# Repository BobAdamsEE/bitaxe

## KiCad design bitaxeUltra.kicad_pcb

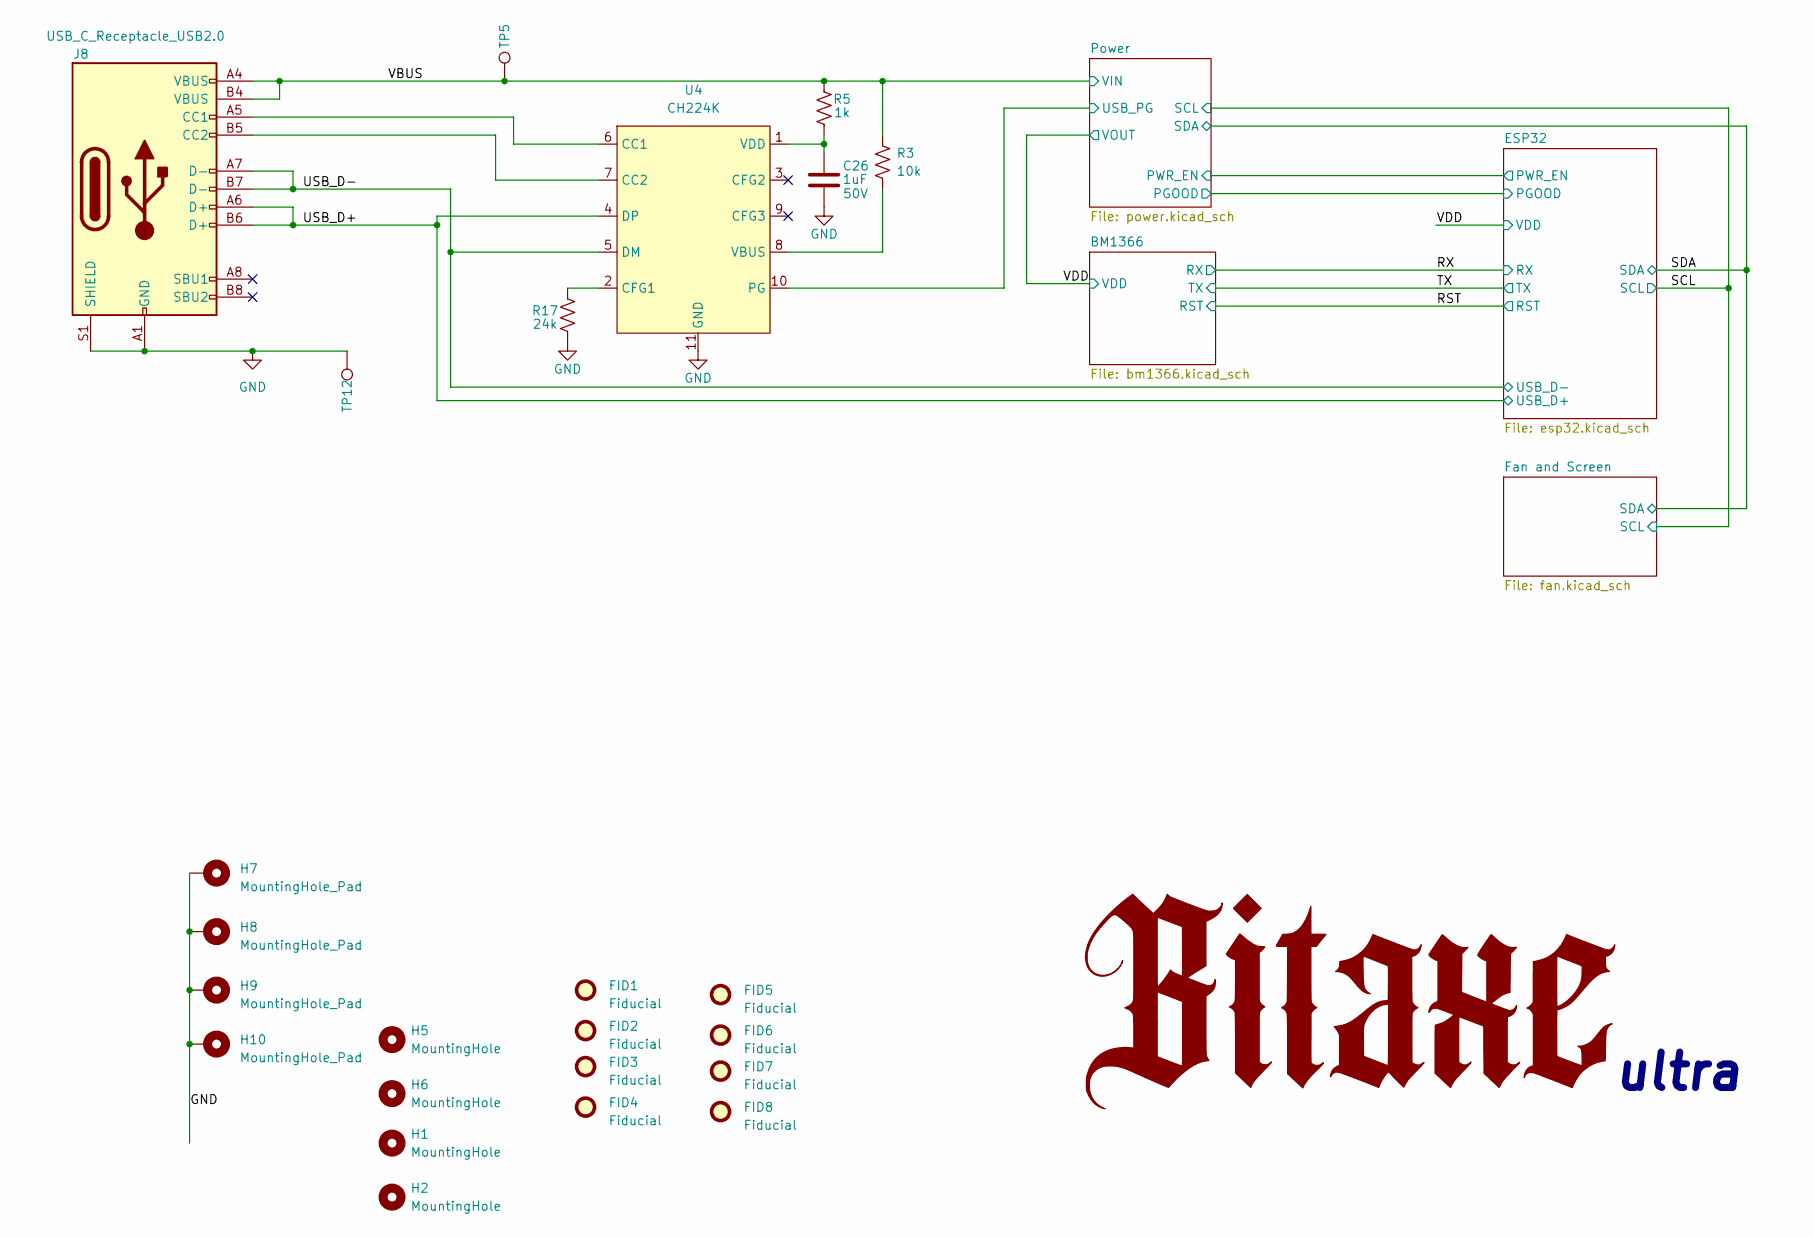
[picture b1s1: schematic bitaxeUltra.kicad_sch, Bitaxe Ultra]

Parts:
C26: 1uF; C_0603_1608Metric; Voltage 50V; PARTNO CC0603KRX7R9BB105
FID1, FID2, FID3, FID4, FID5, FID6, FID7, FID8: Fiducial; Fiducial_1mm_Mask2mm
H1, H2, H5, H6: MountingHole; MountingHole_3.5mm
H7, H8, H9, H10: MountingHole_Pad; MountingHole_3mm_Pad_Via
J8: USB_C_Receptacle_USB2.0; USB_C_Receptacle_GCT_USB4105-xx-A_16P_TopMnt_Horizontal; PARTNO USB4105-GF-A
R3: 10k; R_0402_1005Metric; PARTNO RC0402JR-0710KL
R5: 1k; R_0402_1005Metric; PARTNO RC0402JR-071KL
R17: 24k; R_0402_1005Metric; PARTNO RC0402JR-0724KL
TP5, TP12: TestPoint; TestPoint_Pad_D3.0mm
U4: CH224K; ESSOP-10; PARTNO CH224K

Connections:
/Power/USB_PG: U4.10 (PG); also elsewhere on the board
/USB_D+: J8.A6 (D+), J8.B6 (D+), U4.4 (DP); also elsewhere on the board
/USB_D-: J8.A7 (D-), J8.B7 (D-), U4.5 (DM); also elsewhere on the board
GND: C26.2, H7.1, H8.1, H9.1, H10.1, J8.A1 (GND), J8.B1 (GND), J8.S1 (SHIELD), R17.1, TP12.1, U4.11 (GND); also elsewhere on the board
IN+: J8.A4 (VBUS), J8.B4 (VBUS), R3.1, R5.2, TP5.1; also elsewhere on the board
unnamed: J8.A5 (CC1), U4.6 (CC1)
unnamed: J8.B5 (CC2), U4.7 (CC2)
unnamed: R17.2, U4.2 (CFG1)
unnamed: R3.2, U4.8 (VBUS)
unnamed: C26.1, R5.1, U4.1 (VDD)

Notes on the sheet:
ultra

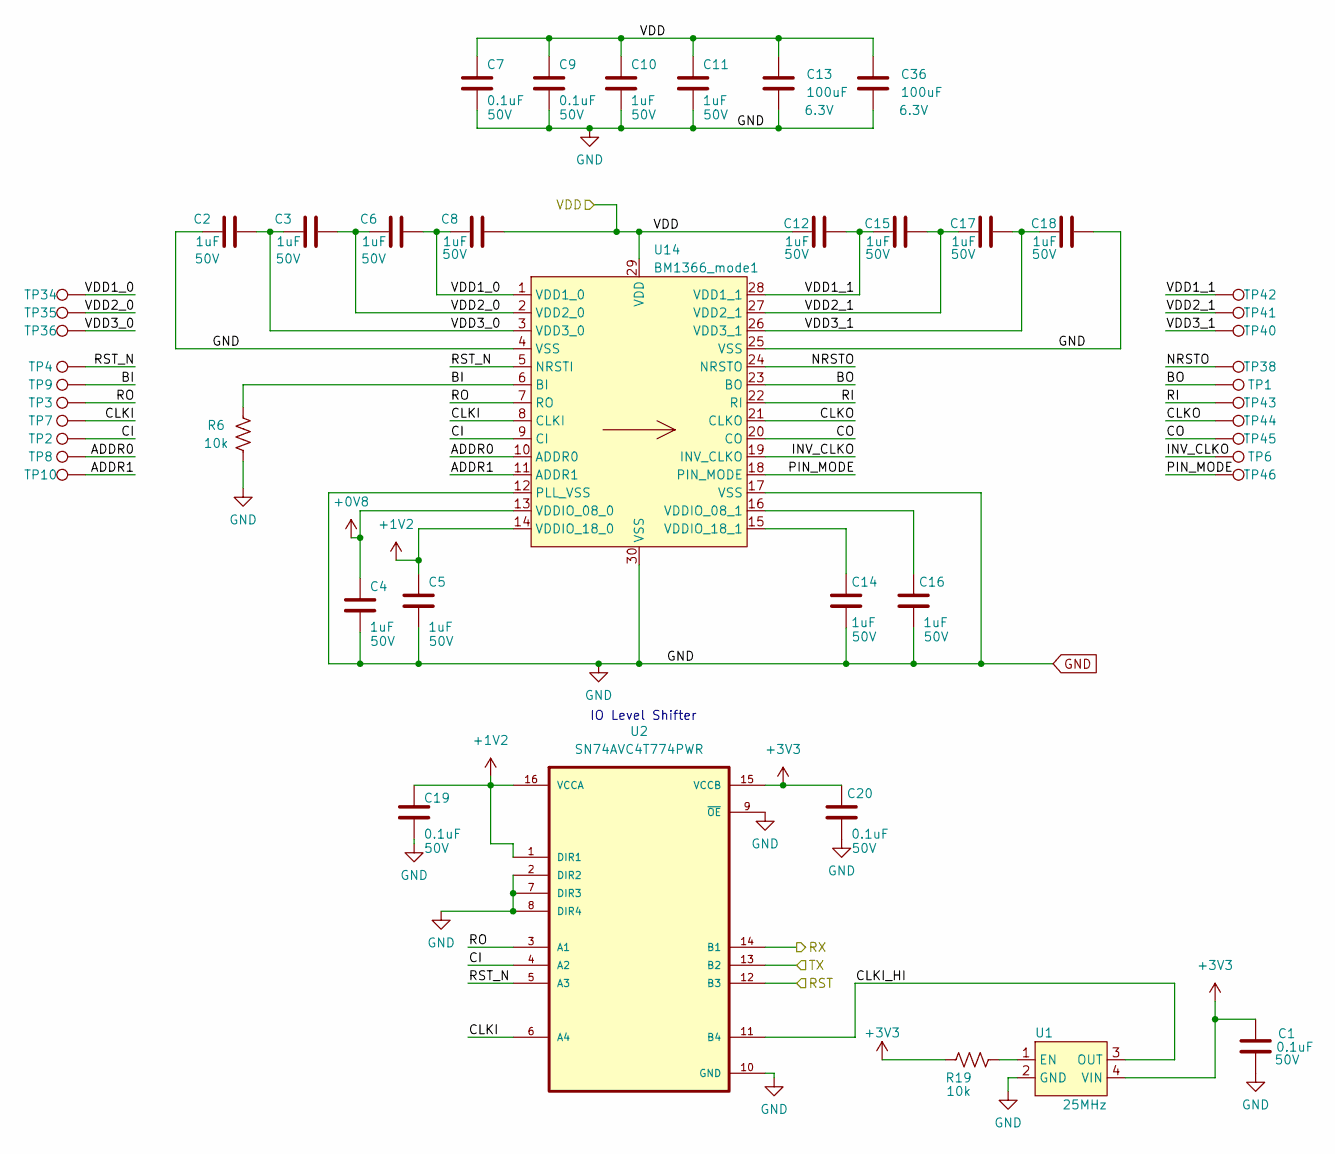
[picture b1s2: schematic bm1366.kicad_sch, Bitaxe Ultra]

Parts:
C1, C7, C9, C19, C20: 0.1uF; C_0402_1005Metric; Voltage 50V; PARTNO GRM155R71H104KE14J
C2, C3, C4, C5, C6, C8, C10, C11, C12, C14, C15, C16, C17, C18: 1uF; C_0603_1608Metric; Voltage 50V; PARTNO CC0603KRX7R9BB105
C13, C36: 100uF; C_1206_3216Metric; Voltage 6.3V; PARTNO GRM31CD80J107MEA8K
R6, R19: 10k; R_0402_1005Metric; PARTNO RC0402JR-0710KL
TP1, TP2, TP3, TP4, TP6, TP7, TP8, TP9, TP10, TP34, TP35, TP36, TP38, TP40, TP41, TP42, TP43, TP44, TP45, TP46: TestPoint; TestPoint_Pad_D1.5mm
U1: 25MHz; O 25,0-JO32-B-1V3-1-T1-LF; PARTNO O 25,0-JO32-B-1V3-1-T1-LF
U2: SN74AVC4T774PWR; SOP65P640X120-16N; PARTNO SN74AVC4T774PWR
U14: BM1366_mode1; BM1366

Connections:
+0V8: C4.1, U14.13 (VDDIO_08_0); also elsewhere on the board
+1V2: C5.1, C19.1, U2.1 (DIR1), U2.16 (VCCA), U14.14 (VDDIO_18_0); also elsewhere on the board
+3V3: C1.2, C20.1, R19.2, U1.4 (VIN), U2.15 (VCCB); also elsewhere on the board
/BM1366/ADDR0: TP8.1, U14.10 (ADDR0)
/BM1366/ADDR1: TP10.1, U14.11 (ADDR1)
/BM1366/BI: R6.2, TP9.1, U14.6 (BI)
/BM1366/BO: TP1.1, U14.23 (BO)
/BM1366/CI: TP2.1, U2.4 (A2), U14.9 (CI)
/BM1366/CLKI: TP7.1, U2.6 (A4), U14.8 (CLKI)
/BM1366/CLKI_HI: U1.3 (OUT), U2.11 (B4)
/BM1366/CLKO: TP44.1, U14.21 (CLKO)
/BM1366/CO: TP45.1, U14.20 (CO)
/BM1366/INV_CLKO: TP6.1, U14.19 (INV_CLKO)
/BM1366/NRSTO: TP38.1, U14.24 (NRSTO)
/BM1366/PIN_MODE: TP46.1, U14.18 (PIN_MODE)
/BM1366/RI: TP43.1, U14.22 (RI)
/BM1366/RO: TP3.1, U2.3 (A1), U14.7 (RO)
/BM1366/RST_N: TP4.1, U2.5 (A3), U14.5 (NRSTI)
/BM1366/VDD1_0: C6.2, C8.1, TP34.1, U14.1 (VDD1_0)
/BM1366/VDD1_1: C12.2, C15.1, TP42.1, U14.28 (VDD1_1)
/BM1366/VDD2_0: C3.2, C6.1, TP35.1, U14.2 (VDD2_0)
/BM1366/VDD2_1: C15.2, C17.1, TP41.1, U14.27 (VDD2_1)
/BM1366/VDD3_0: C2.2, C3.1, TP36.1, U14.3 (VDD3_0)
/BM1366/VDD3_1: C17.2, C18.1, TP40.1, U14.26 (VDD3_1)
/RST: U2.12 (B3); also elsewhere on the board
/RX: U2.14 (B1); also elsewhere on the board
/TX: U2.13 (B2); also elsewhere on the board
/VDD: C7.1, C8.2, C9.1, C10.1, C11.1, C12.1, C13.1, C36.1, U14.29 (VDD); also elsewhere on the board
GND: C1.1, C2.1, C4.2, C5.2, C7.2, C9.2, C10.2, C11.2, C13.2, C14.2, C16.2, C18.2, C19.2, C20.2, C36.2, R6.1, U1.2 (GND), U2.2 (DIR2), U2.7 (DIR3), U2.8 (DIR4), U2.9 (~OE), U2.10 (GND), U14.4 (VSS), U14.12 (PLL_VSS), U14.17 (VSS), U14.25 (VSS), U14.30 (VSS); also elsewhere on the board
unnamed: R19.1, U1.1 (EN)
unnamed: C16.1, U14.16 (VDDIO_08_1)
unnamed: C14.1, U14.15 (VDDIO_18_1)

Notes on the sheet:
IO Level Shifter

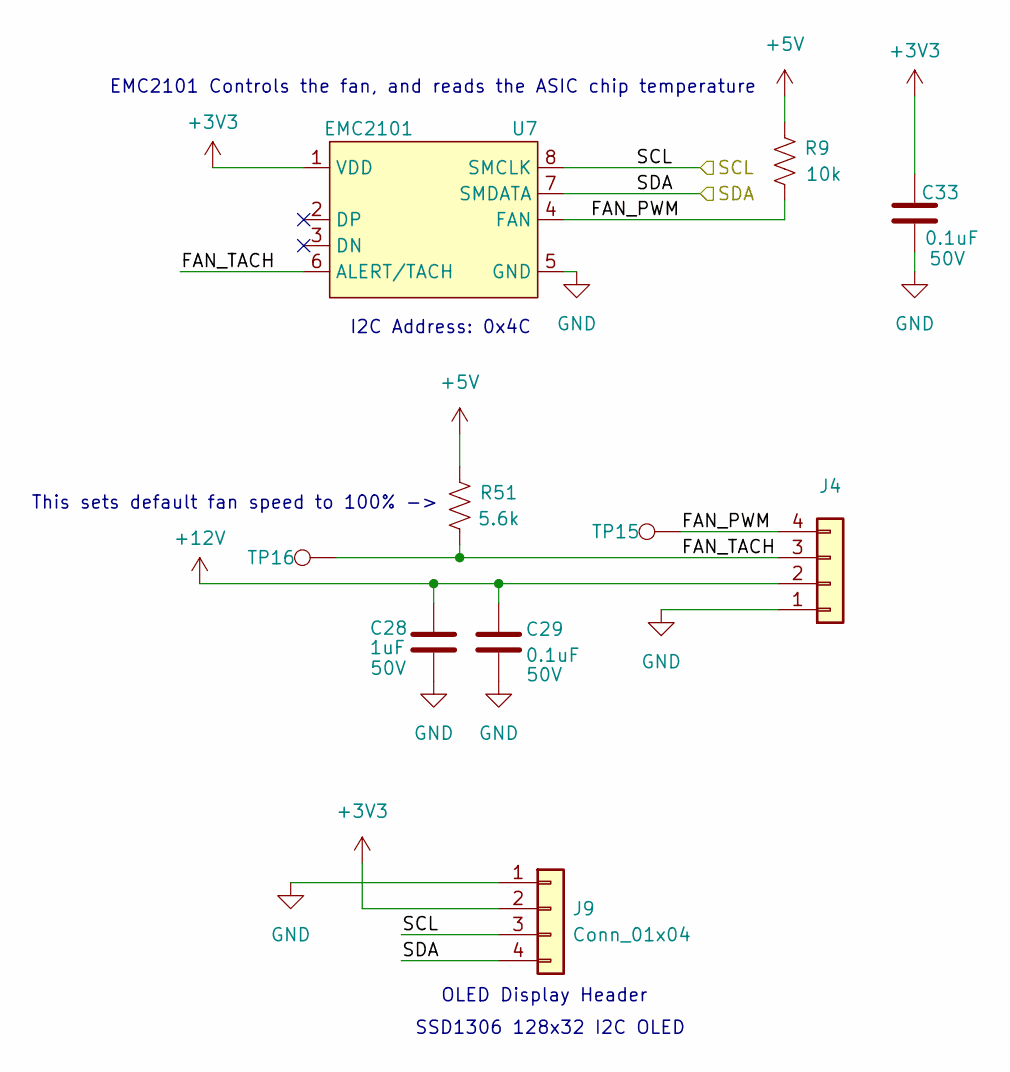
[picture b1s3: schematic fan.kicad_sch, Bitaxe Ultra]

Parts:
C28: 1uF; C_0603_1608Metric; Voltage 50V; PARTNO CC0603KRX7R9BB105
C29, C33: 0.1uF; C_0402_1005Metric; Voltage 50V; PARTNO GRM155R71H104KE14J
J4: Conn_01x04; 470531000; PARTNO 0470531000
J9: Conn_01x04; PinHeader_1x04_P2.54mm_Vertical_shifted; PARTNO NPTC041KFXC-RC
R9: 10k; R_0402_1005Metric; PARTNO RC0402JR-0710KL
R51: 5.6k; R_0402_1005Metric; PARTNO RC0402FR-135K6L
TP15, TP16: TestPoint; TestPoint_Pad_D1.5mm
U7: EMC2101; TSSOP-8_3x3mm_P0.65mm; PARTNO EMC2101-R-ACZL-TR

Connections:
+3V3: C33.1, J9.2, U7.1 (VDD); also elsewhere on the board
+5V: R9.2; also elsewhere on the board
+12V: C28.1, C29.1, J4.2; also elsewhere on the board
/Fan and Screen/FAN_PWM: J4.4, R9.1, TP15.1, U7.4 (FAN)
/Fan and Screen/FAN_TACH: J4.3, TP16.1, U7.6 (ALERT/TACH); also elsewhere on the board
/SCL: J9.3, U7.8 (SMCLK); also elsewhere on the board
/SDA: J9.4, U7.7 (SMDATA); also elsewhere on the board
GND: C28.2, C29.2, C33.2, J4.1, J9.1, U7.5 (GND); also elsewhere on the board

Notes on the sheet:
SSD1306 128x32 I2C OLED
EMC2101 Controls the fan, and reads the ASIC chip temperature
This sets default fan speed to 100% ->
OLED Display Header
I2C Address: 0x4C

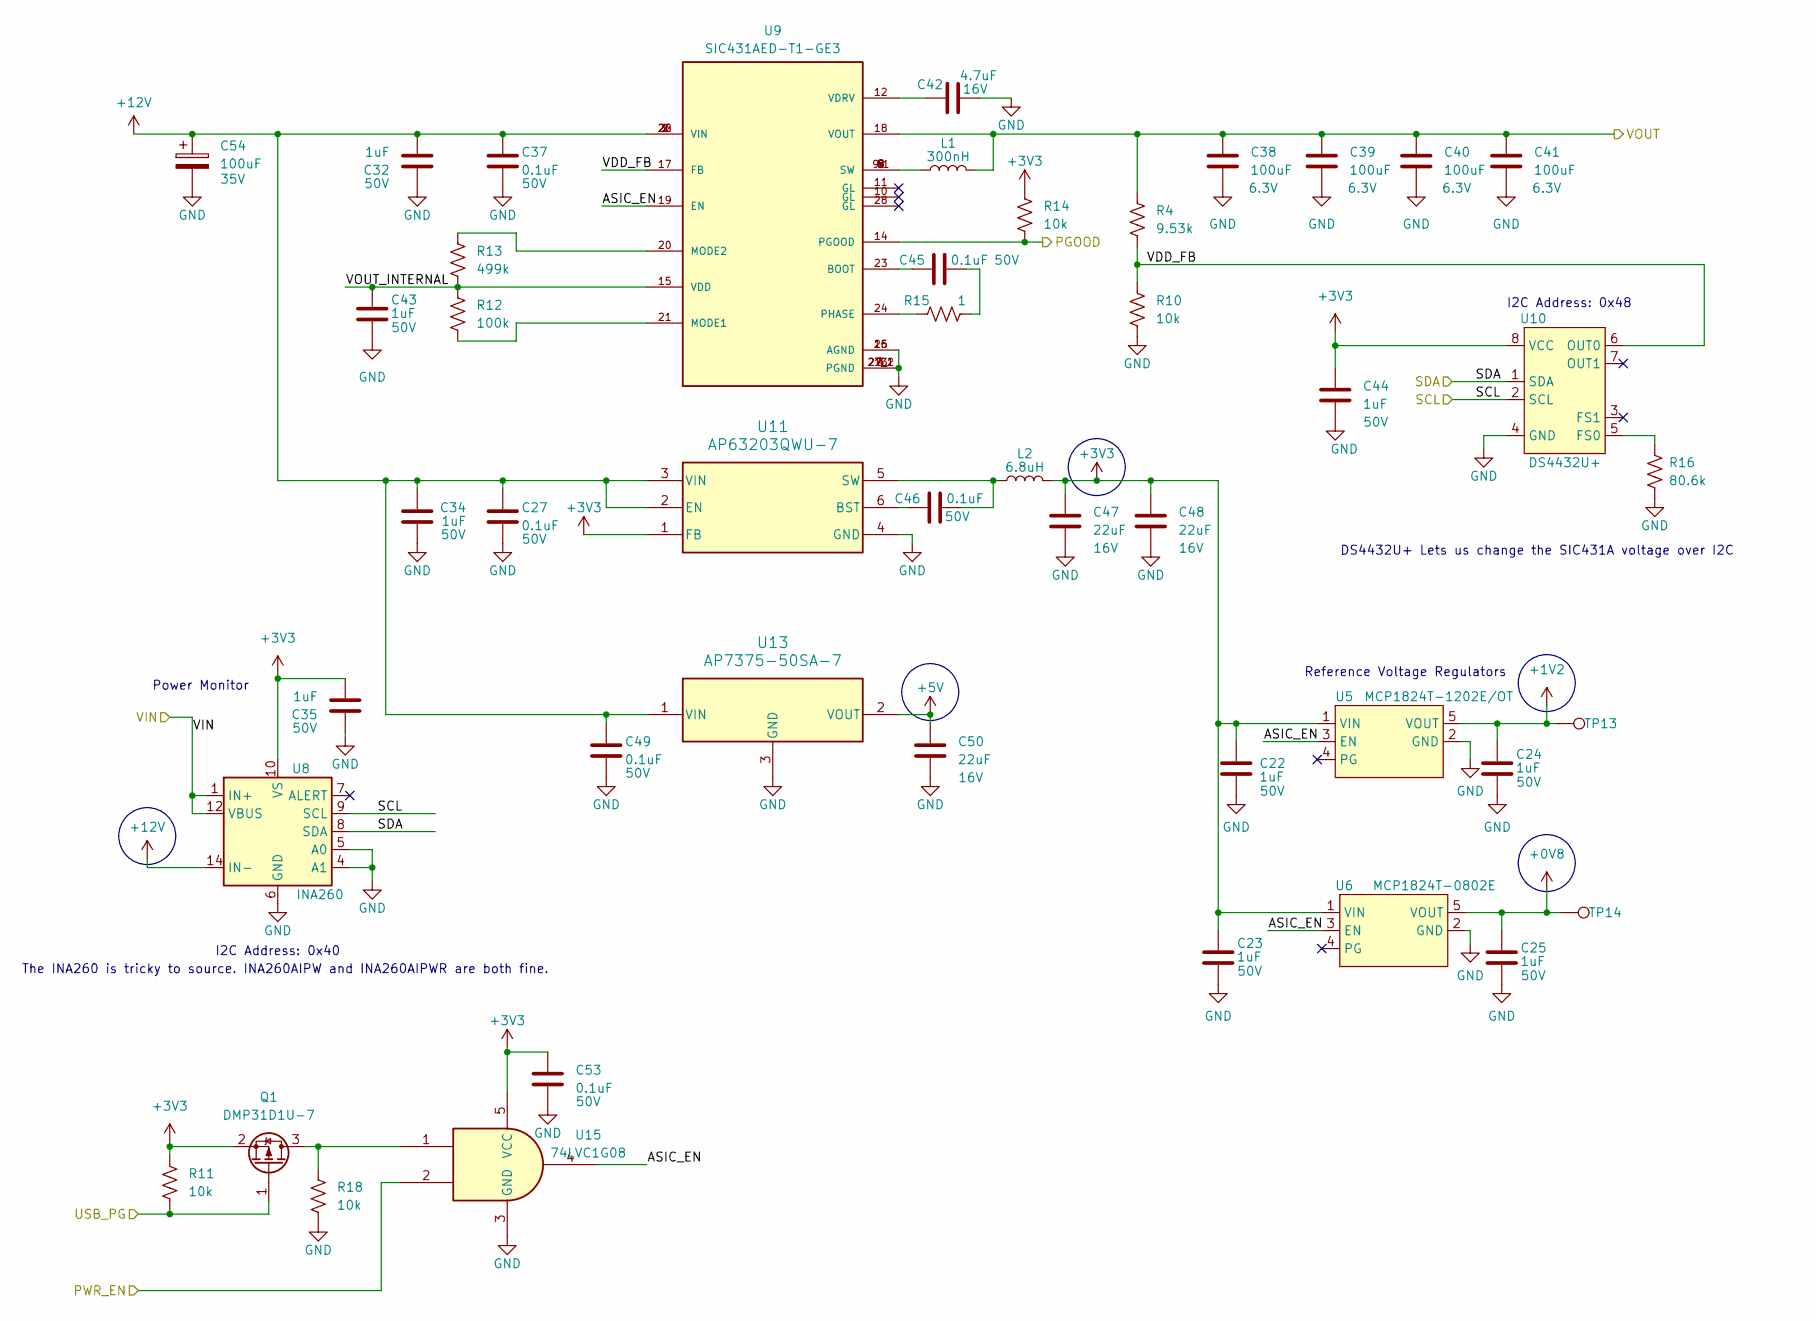
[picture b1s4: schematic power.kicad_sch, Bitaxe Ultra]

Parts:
C22, C23, C24, C25, C32, C34, C35, C43, C44: 1uF; C_0603_1608Metric; Voltage 50V; PARTNO CC0603KRX7R9BB105
C27, C37, C45, C46, C49, C53: 0.1uF; C_0402_1005Metric; Voltage 50V; PARTNO GRM155R71H104KE14J
C38, C39, C40, C41: 100uF; C_1206_3216Metric; Voltage 6.3V; PARTNO GRM31CD80J107MEA8K
C42: 4.7uF; C_0805_2012Metric; Voltage 16V; PARTNO GRM21BR71C475KE51K
C47, C48, C50: 22uF; C_0805_2012Metric; Voltage 16V; PARTNO GRM21BC81C226ME44L
C54: 100uF; CAP_WCAP-ASLI_06p3X07p7_WRE; Voltage 35V; PARTNO 865080545012
L1: 300nH; INDUCTOR_SPB1007-R30M; PARTNO SPB1007-R30M
L2: 6.8uH; IND_VLS5045EX-100M; PARTNO VLS5045EX-6R8M
Q1: DMP31D1U-7; DIODESINC_SOT-23; PARTNO DMP31D1U-7
R4: 9.53k; R_0402_1005Metric; PARTNO RC0402FR-079K53L
R10, R11, R14, R18: 10k; R_0402_1005Metric; PARTNO RC0402JR-0710KL
R12: 100k; R_0402_1005Metric; PARTNO RC0402FR-07100KL
R13: 499k; R_0402_1005Metric; PARTNO RC0402FR-07499KL
R15: 1; R_0402_1005Metric; PARTNO RC0402JR-071RL
R16: 80.6k; R_0402_1005Metric; PARTNO RC0402FR-0780K6L
TP13, TP14: TestPoint; TestPoint_Pad_D1.5mm
U5: MCP1824T-1202E/OT; SOT-23-5; PARTNO MCP1824T-1202E/OT
U6: MCP1824T-0802E; SOT-23-5; PARTNO MCP1824T-0802E/OT
U8: INA260; TSSOP-16_4.4x5mm_P0.65mm; PARTNO INA260AIPW
U9: SIC431AED-T1-GE3; REGULATOR_SIC431AED-T1-GE3; PARTNO SIC431AED-T1-GE3
U10: DS4432U+; TSSOP-8_3x3mm_P0.65mm; PARTNO DS4432U+
U11: AP63203QWU-7; TSOT26_DIO; PARTNO AP63203QWU-7
U13: AP7375-50SA-7; DIODESINC_SOT-23; PARTNO AP7375-50SA-7
U15: 74LVC1G08; SOT-353_SC-70-5; PARTNO 74LVC1G08GW,125

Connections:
+0V8: C25.1, TP14.1, U6.5 (VOUT); also elsewhere on the board
+1V2: C24.1, TP13.1, U5.5 (VOUT); also elsewhere on the board
+3V3: C22.1, C23.1, C35.2, C44.1, C47.1, C48.1, C53.1, L2.2, Q1.2 (S), R11.1, R14.1, U5.1 (VIN), U6.1 (VIN), U8.10 (VS), U10.8 (VCC), U11.1 (FB), U15.5 (VCC); also elsewhere on the board
+5V: C50.1, U13.2 (VOUT); also elsewhere on the board
+12V: C27.1, C32.2, C34.2, C37.1, C49.1, C54.1, U8.14 (IN-), U8.15 (IN-), U8.16 (IN-), U9.1 (VIN), U9.2 (VIN), U9.22 (VIN), U9.26 (VIN), U11.2 (EN), U11.3 (VIN), U13.1 (VIN); also elsewhere on the board
/ESP32/PGOOD: R14.2, U9.14 (PGOOD); also elsewhere on the board
/ESP32/PWR_EN: U15.2; also elsewhere on the board
/Power/ASIC_EN: U5.3 (EN), U6.3 (EN), U9.19 (EN), U15.4
/Power/USB_PG: Q1.1 (G), R11.2; also elsewhere on the board
/Power/VDD_FB: R4.2, R10.1, U9.17 (FB), U10.6 (OUT0)
/Power/VOUT_INTERNAL: C43.1, R12.1, R13.2, U9.15 (VDD)
/SCL: U8.9 (SCL), U10.2 (SCL); also elsewhere on the board
/SDA: U8.8 (SDA), U10.1 (SDA); also elsewhere on the board
/VDD: C38.1, C39.1, C40.1, C41.1, L1.2, R4.1, U9.18 (VOUT); also elsewhere on the board
GND: C22.2, C23.2, C24.2, C25.2, C27.2, C32.1, C34.1, C35.1, C37.2, C38.2, C39.2, C40.2, C41.2, C42.2, C43.2, C44.2, C47.2, C48.2, C49.2, C50.2, C53.2, C54.2, R10.2, R16.2, R18.2, U5.2 (GND), U6.2 (GND), U8.4 (A1), U8.5 (A0), U8.6 (GND), U8.11 (GND), U9.3 (PGND), U9.4 (PGND), U9.13 (PGND), U9.16 (AGND), U9.25 (AGND), U9.27_1 (PGND), U9.27_2 (PGND), U10.4 (GND), U11.4 (GND), U13.3 (GND), U15.3 (GND); also elsewhere on the board
IN+: U8.1 (IN+), U8.2 (IN+), U8.3 (IN+), U8.12 (VBUS); also elsewhere on the board
unnamed: C45.2, R15.2
unnamed: L1.1, U9.5 (SW), U9.6 (SW), U9.7 (SW), U9.8 (SW), U9.9 (SW), U9.9.1 (SW)
unnamed: Q1.3 (D), R18.1, U15.1
unnamed: C45.1, U9.23 (BOOT)
unnamed: R12.2, U9.21 (MODE1)
unnamed: R13.1, U9.20 (MODE2)
unnamed: R15.1, U9.24 (PHASE)
unnamed: C42.1, U9.12 (VDRV)
unnamed: R16.1, U10.5 (FS0)
unnamed: C46.1, U11.6 (BST)
unnamed: C46.2, L2.1, U11.5 (SW)

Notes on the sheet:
DS4432U+ Lets us change the SIC431A voltage over I2C
I2C Address: 0x48
The INA260 is tricky to source. INA260AIPW and INA260AIPWR are both fine.
Power Monitor
Reference Voltage Regulators
I2C Address: 0x40

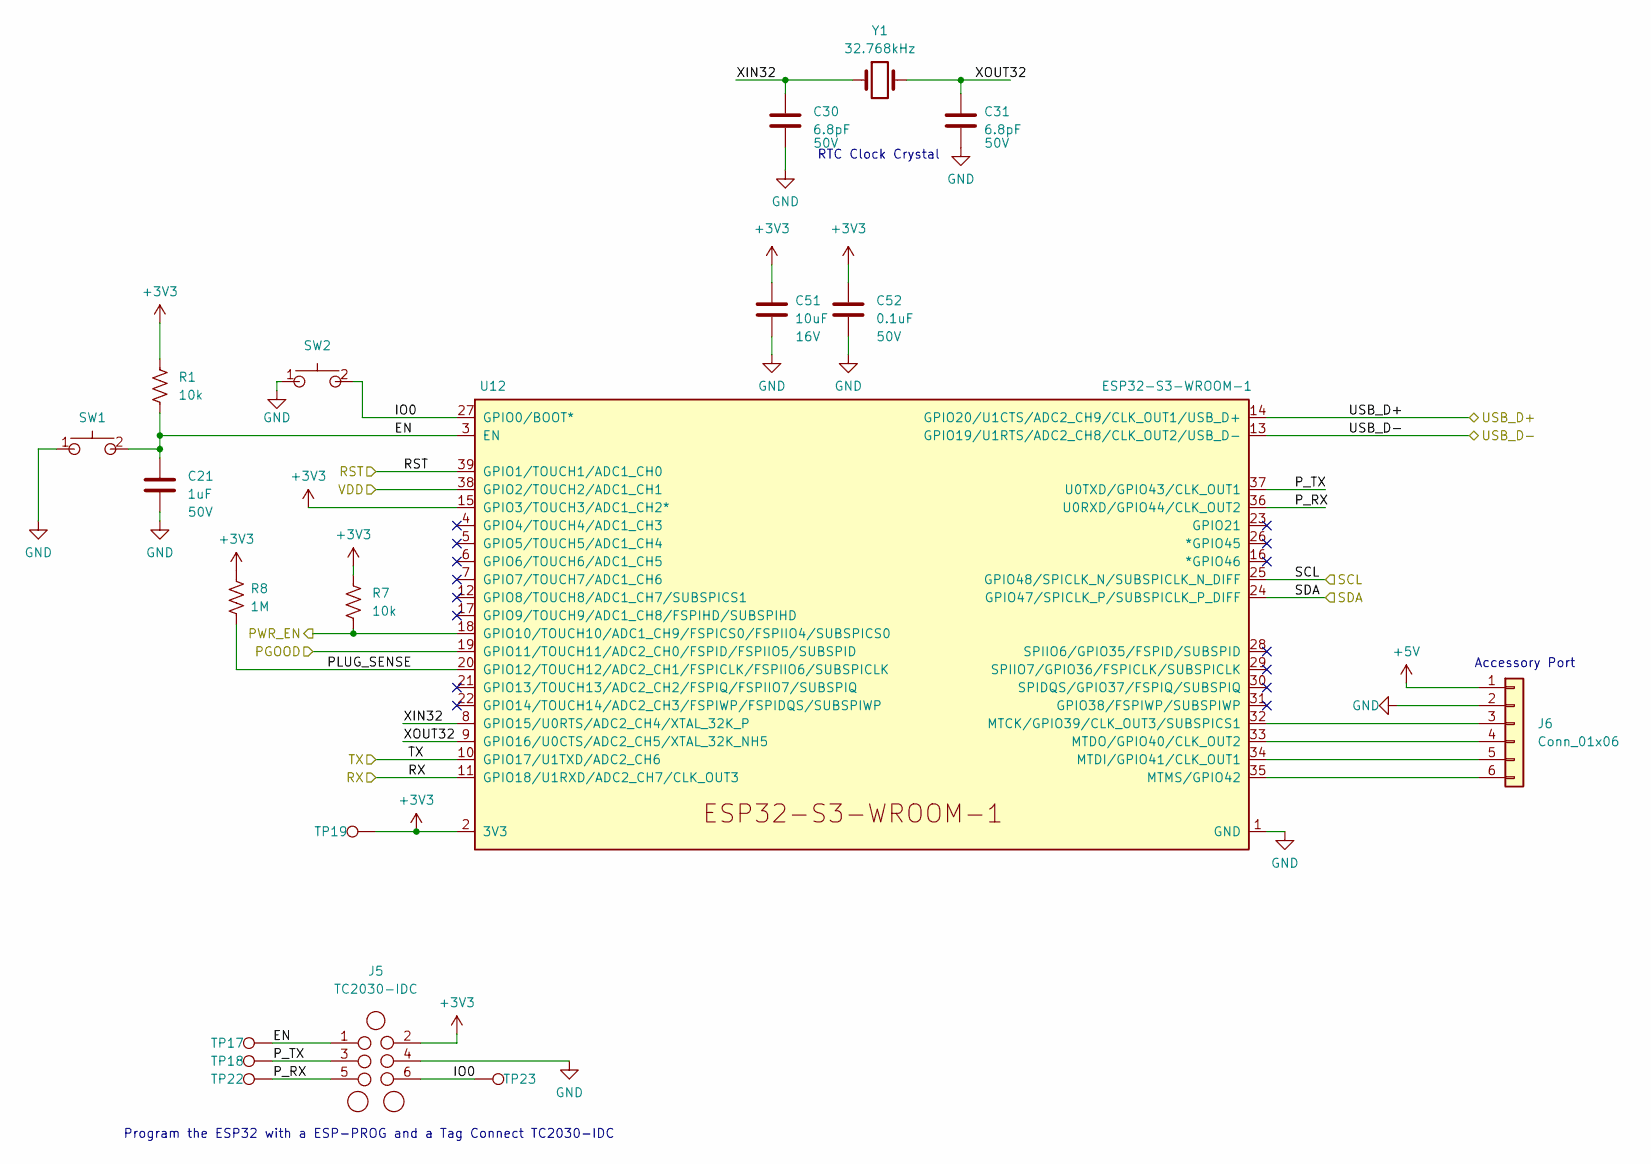
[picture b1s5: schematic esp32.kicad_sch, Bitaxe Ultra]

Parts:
C21: 1uF; C_0603_1608Metric; Voltage 50V; PARTNO CC0603KRX7R9BB105
C30, C31: 6.8pF; C_0402_1005Metric; Voltage 50V; PARTNO C0402C689C5GAC7867
C51: 10uF; C_0805_2012Metric; Voltage 16V; PARTNO CL21A106KOQNNNE
C52: 0.1uF; C_0402_1005Metric; Voltage 50V; PARTNO GRM155R71H104KE14J
J5: TC2030-IDC; Tag-Connect_TC2030-IDC-NL_2x03_P1.27mm_Vertical
J6: Conn_01x06; PinHeader_1x06_P2.54mm_Vertical
R1, R7: 10k; R_0402_1005Metric; PARTNO RC0402JR-0710KL
R8: 1M; R_0402_1005Metric; PARTNO RC0402FR-071ML
SW1, SW2: GT-TC029B-H025-L1N; SW_CS1213AGF260_CRS; PARTNO CS1213AGF260
TP17, TP18, TP19, TP22, TP23: TestPoint; TestPoint_Pad_D1.5mm
U12: ESP32-S3-WROOM-1; PARTNO ESP32-S3-WROOM-1-N16R8
Y1: 32.768kHz; SC32S-7PF20PPM; PARTNO SC32S-7PF20PPM

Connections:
+3V3: C51.1, C52.1, J5.2, R1.1, R7.1, R8.1, TP19.1, U12.2 (3V3), U12.15 (GPIO3/TOUCH3/ADC1_CH2*); also elsewhere on the board
+5V: J6.1; also elsewhere on the board
/ESP32/EN: C21.1, J5.1, R1.2, SW1.2, TP17.1, U12.3 (EN)
/ESP32/IO0: J5.6, SW2.2, TP23.1, U12.27 (GPIO0/BOOT*)
/ESP32/PGOOD: U12.19 (GPIO11/TOUCH11/ADC2_CH0/FSPID/FSPIIO5/S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); also elsewhere on the board
/ESP32/PLUG_SENSE: R8.2, U12.20 (GPIO12/TOUCH12/ADC2_CH1/FSPICLK/FSPIIO6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)
/ESP32/PWR_EN: R7.2, U12.18 (GPIO10/TOUCH10/ADC1_CH9/FSPICS0/FSPIIO4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); also elsewhere on the board
/ESP32/P_RX: J5.5, TP22.1, U12.36 (U0RXD/GPIO44/CLK_OUT2)
/ESP32/P_TX: J5.3, TP18.1, U12.37 (U0TXD/GPIO43/CLK_OUT1)
/ESP32/XIN32: C30.1, U12.8 (GPIO15/U0RTS/ADC2_CH4/XTAL_32K_P), Y1.1
/ESP32/XOUT32: C31.1, U12.9 (GPIO16/U0CTS/ADC2_CH5/XTAL_32K_NH5), Y1.2
/RST: U12.39 (GPIO1/TOUCH1/ADC1_CH0); also elsewhere on the board
/RX: U12.11 (GPIO18/U1RXD/ADC2_CH7/CLK_OUT3); also elsewhere on the board
/SCL: U12.25 (GPIO48/SPICLK_N/SUBSPICLK_N_DIFF); also elsewhere on the board
/SDA: U12.24 (GPIO47/SPICLK_P/SUBSPICLK_P_DIFF); also elsewhere on the board
/TX: U12.10 (GPIO17/U1TXD/ADC2_CH6); also elsewhere on the board
/USB_D+: U12.14 (GPIO20/U1CTS/ADC2_CH9/CLK_OUT1/USB_D+); also elsewhere on the board
/USB_D-: U12.13 (GPIO19/U1RTS/ADC2_CH8/CLK_OUT2/USB_D-); also elsewhere on the board
/VDD: U12.38 (GPIO2/TOUCH2/ADC1_CH1); also elsewhere on the board
GND: C21.2, C30.2, C31.2, C51.2, C52.2, J5.4, J6.2, SW1.1, SW2.1, U12.1 (GND), U12.40 (GND), U12.41 (GND); also elsewhere on the board
unnamed: J6.3, U12.32 (MTCK/GPIO39/CLK_OUT3/SUBSPICS1)
unnamed: J6.4, U12.33 (MTDO/GPIO40/CLK_OUT2)
unnamed: J6.5, U12.34 (MTDI/GPIO41/CLK_OUT1)
unnamed: J6.6, U12.35 (MTMS/GPIO42)

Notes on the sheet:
Accessory Port
RTC Clock Crystal
Program the ESP32 with a ESP-PROG and a Tag Connect TC2030-IDC

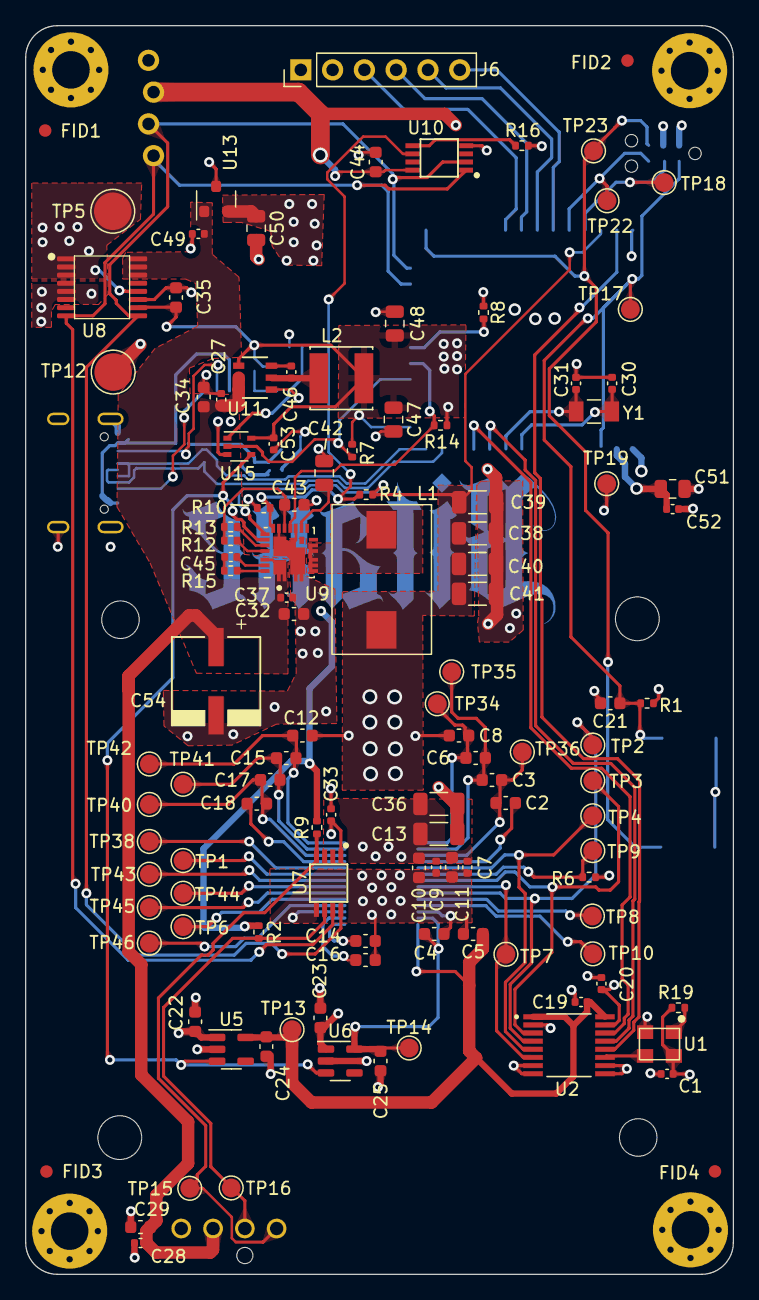
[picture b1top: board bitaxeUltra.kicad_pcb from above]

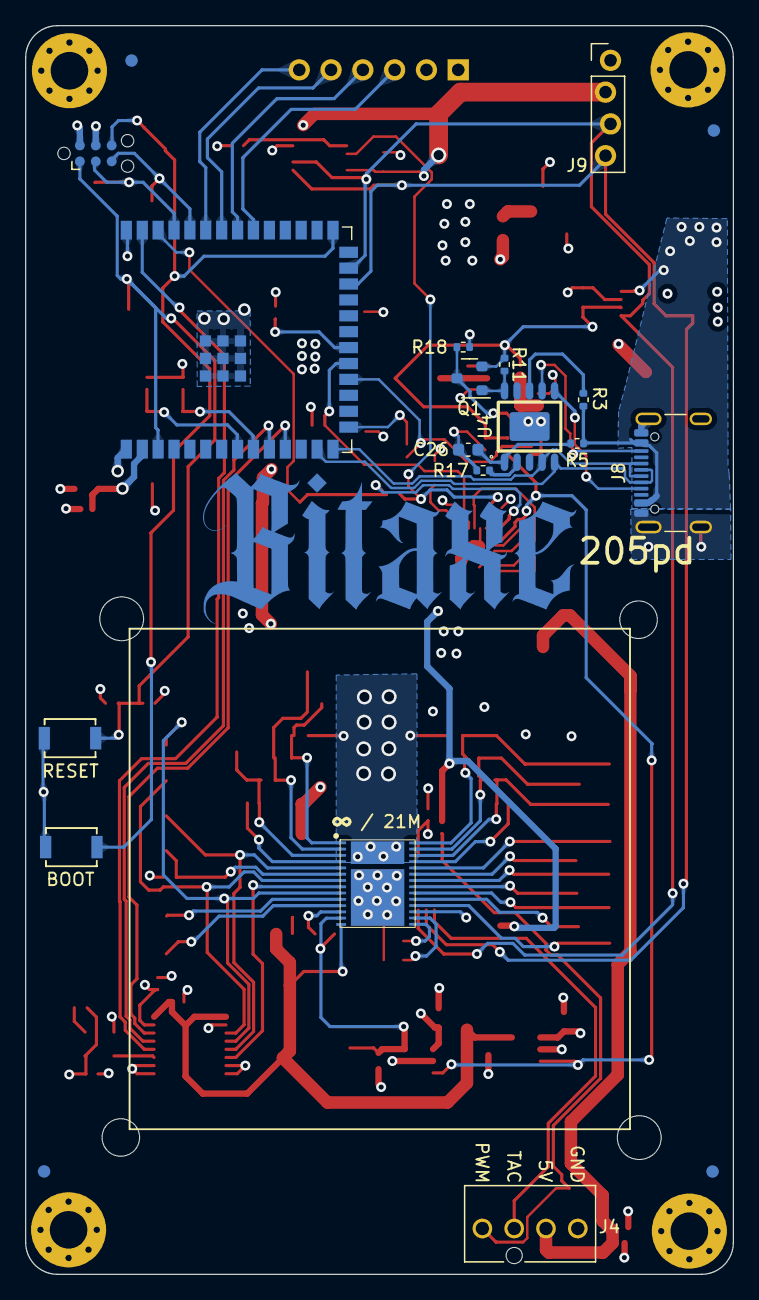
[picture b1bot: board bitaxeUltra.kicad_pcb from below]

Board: 4 copper layers, 56.5 x 99.8 mm, 145 parts (20 on the bottom side), 74 nets.

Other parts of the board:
R2: 5.6k; R_0402_1005Metric

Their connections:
+5V: R2.2; also elsewhere on the board
/Fan and Screen/FAN_TACH: R2.1; also elsewhere on the board

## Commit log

2024-02-14 Power analysis; updates to 205pd
    Started analysis based on the 204 with an architecture diagram and with an smath document. Copied over manually changes from the 205 branch and started updating the schematic with USB PD capabilities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
2024-02-16 Worked on VDD
    Started importing SiC431A for VDD supply. Yet to do Vfb, Mode, Pgood, boot, phase, en. Moved power supplies to power page. Configured CH224K to 12V
2024-02-27 SCH Draft 3, PCB Start
    Finished some last minute changes to change 1V8 to 1V2 based on discord feedback. Updated level shifter and moved 25MHz oscillator to use 3V3 and be shifted down. Started working on layout.
2024-02-27 PCB Work
    Parts now all within board but various issues still exist. Routing started, placement needs to be refined.
2024-02-29 3.3V net fix, PCB progress
    Fixed accidental use of both 3V3 and 3.3V to just use 3V3. Worked on PCB
2024-02-29 Layout work
    Working on power supplies - moved VDD south, added nice planes for it. Started cleaning up around new level shifter.
2024-03-04 Layout completed for concept 1
    Need to still work on vias and fills, move some parts around.
2024-03-12 Release Candidate 205pd
    Everything ordered. Let's see how it goes!
2024-03-21 KiCad 8 + InteractiveHTMLBOM
    Updated to KiCad 8 and some auto-conversions occurred. Generated interactive HTML BOM to prepare for assembly.
